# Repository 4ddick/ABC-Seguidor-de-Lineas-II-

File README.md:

Seguidor-de-linea-ABCII
Seguidor de linea modelo ABC (versión.II)

Durante el presente año, los integrantes del equipo "ABC" han asumido el compromiso de desarrollar un nuevo diseño del proyecto previo denominado "Robot seguidor de línea ABC I". El rediseño contempla modificaciones estructurales y funcionales orientadas a optimizar el desempeño del sistema, incrementar la precisión en el seguimiento de trayectorias y mejorar la interacción con el usuario.

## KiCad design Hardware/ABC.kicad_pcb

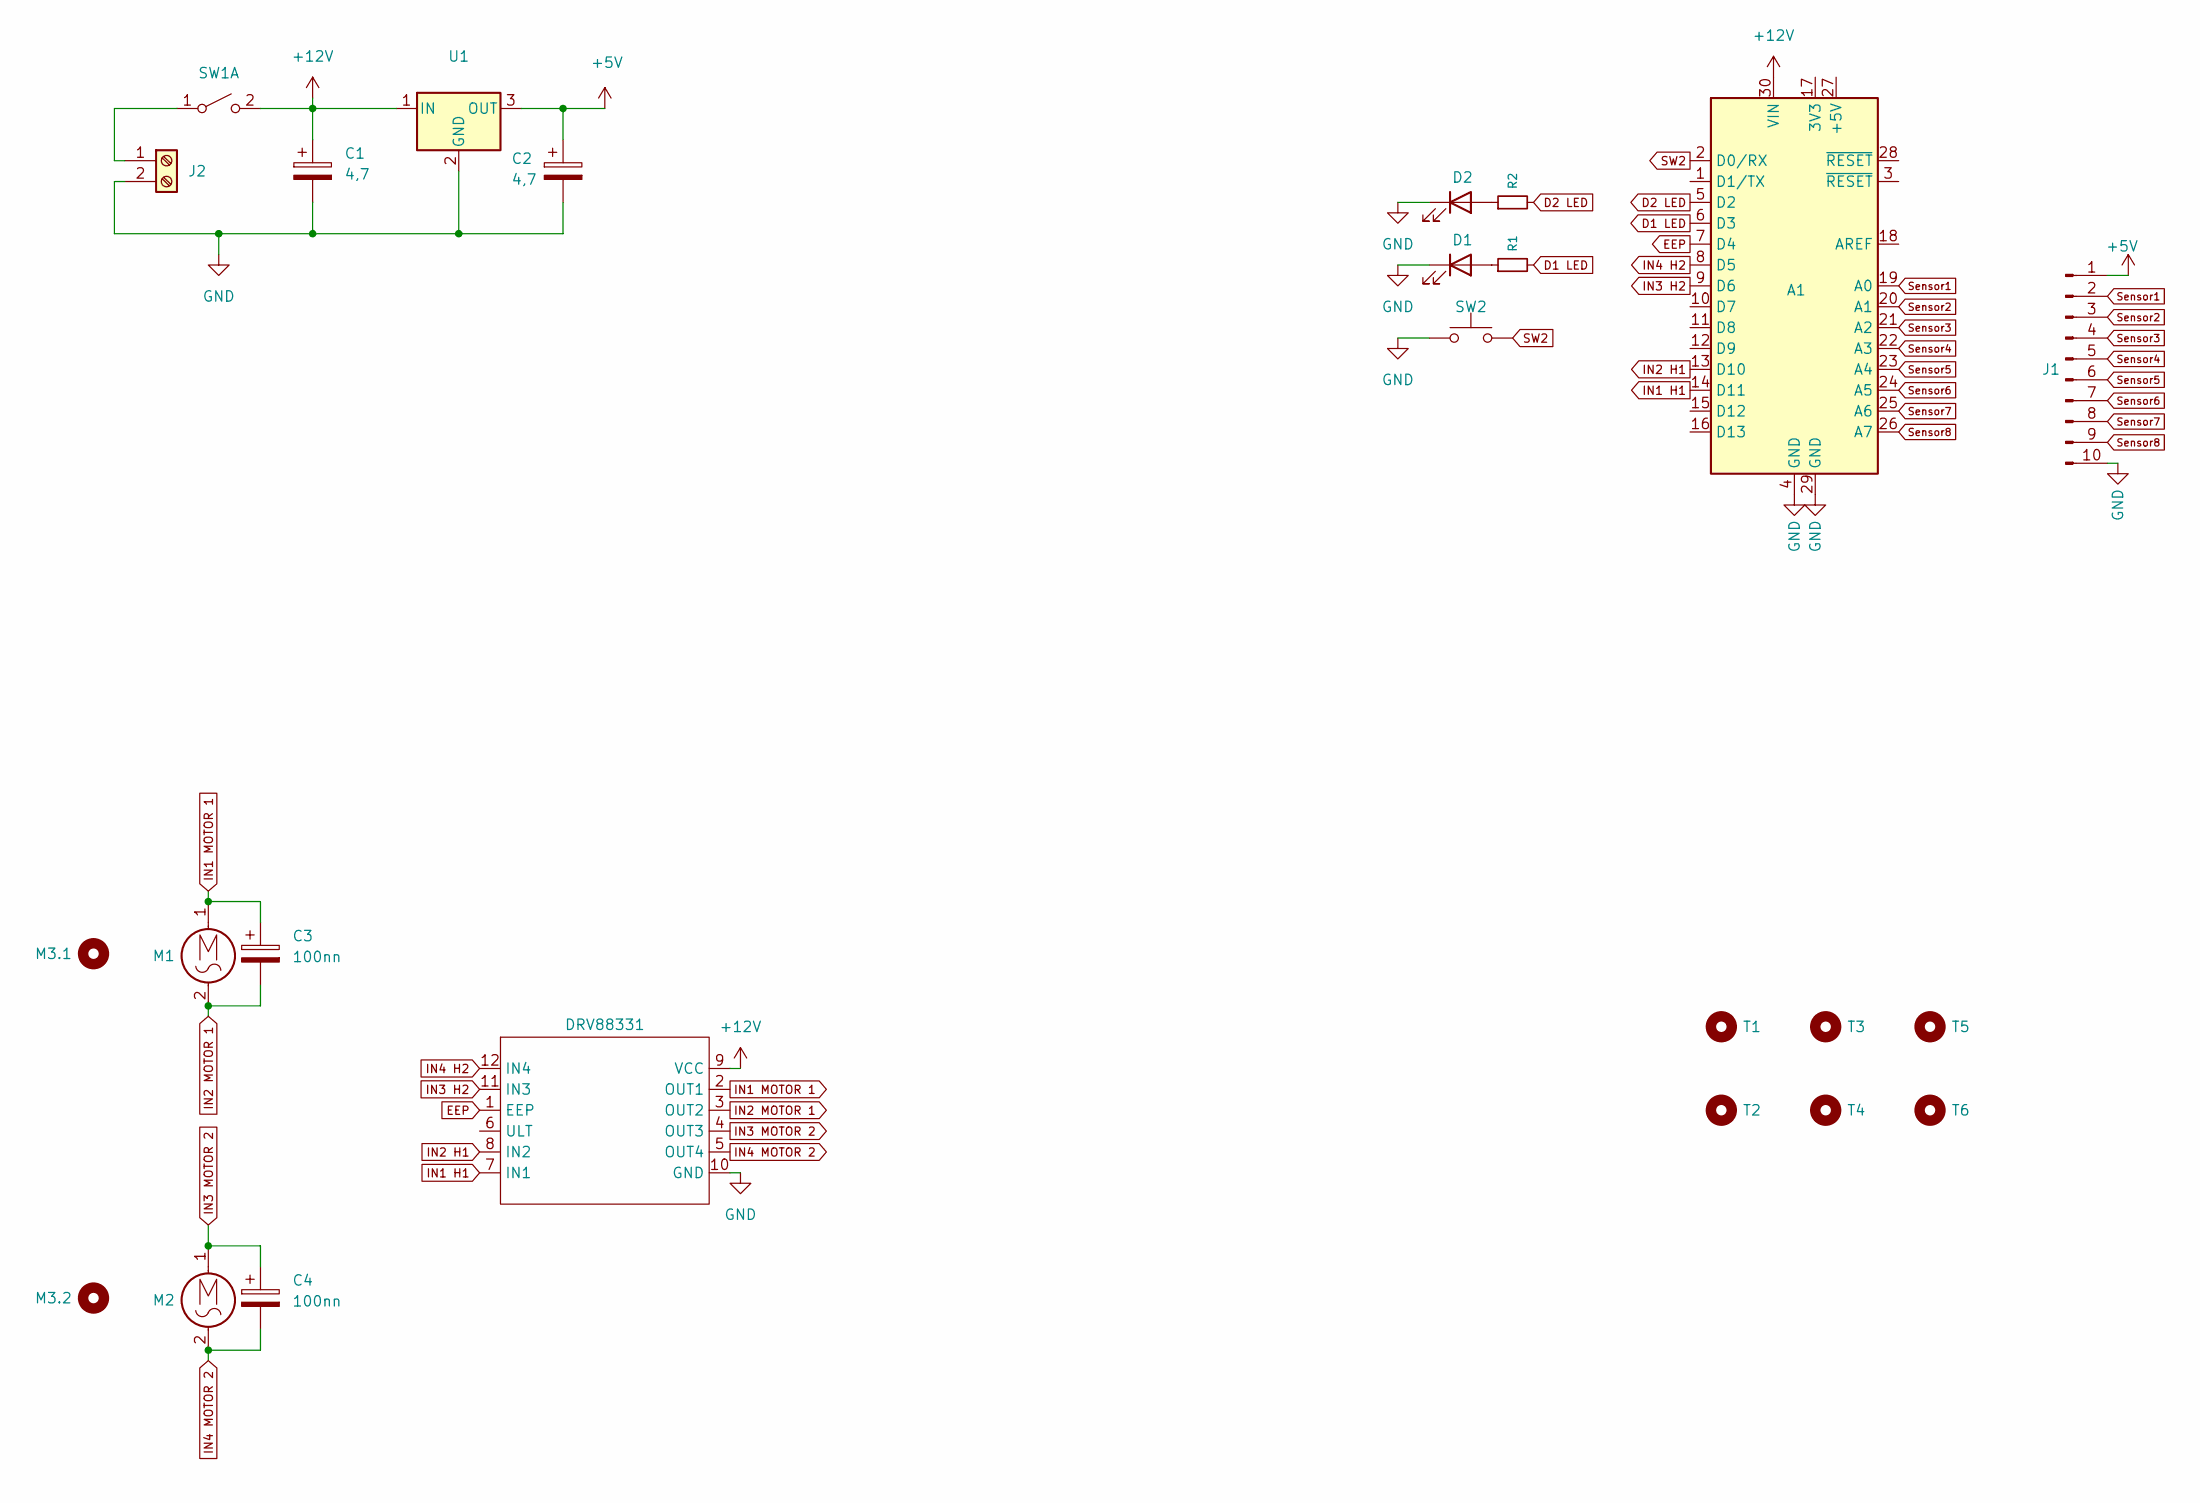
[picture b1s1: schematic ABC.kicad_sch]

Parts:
A1: Arduino_Nano_v2.x; Arduino_Nano
C1, C2: 4,7; CP_Radial_D6.3mm_P2.50mm
C3, C4: 100nn; C_Disc_D5.0mm_W2.5mm_P5.00mm
D1, D2: LED; LED_D5.0mm
DRV88331: PUENTE H1; DRV8833_MODULE
J1: Conn_01x10_Pin; PinHeader_1x10_P2.54mm_Vertical
J2: XT30AWM
M1, M2: Motor_AC; PinHeader_1x02_P2.54mm_Vertical
M3.1, M3.2: Mounting_Hole; Pololu_Micro_Bracket_Wheel_42mm
R1, R2: R_Small; R_Axial_DIN0207_L6.3mm_D2.5mm_P7.62mm_Horizontal
SW1: SW_DPST_x2; TerminalBlock_MaiXu_MX126-5.0-03P_1x03_P5.00mm
SW2: SW_PUSH; Button
T1, T2, T3, T4, T5, T6: Mounting_Hole; MountingHole_3.2mm_M3
U1: L7805; TO-220-3_Vertical

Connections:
+5V: C2.1, J1.1, U1.3 (OUT)
+12V: A1.30 (VIN), C1.1, DRV88331.9 (VCC), SW1.2 (B), SW1.3 (A), U1.1 (IN)
D1 LED: A1.6 (D3), R1.2
D2 LED: A1.5 (D2), R2.2
EEP: A1.7 (D4), DRV88331.1 (EEP)
GND: A1.4 (GND), A1.29 (GND), C1.2, C2.2, D1.1 (K), D2.1 (K), DRV88331.10 (GND), J1.10, J2.2, SW2.1, U1.2 (GND)
IN1 H1: A1.14 (D11), DRV88331.7 (IN1)
IN1 MOTOR 1: C3.1, DRV88331.2 (OUT1), M1.1
IN2 H1: A1.13 (D10), DRV88331.8 (IN2)
IN2 MOTOR 1: C3.2, DRV88331.3 (OUT2), M1.2
IN3 H2: A1.9 (D6), DRV88331.11 (IN3)
IN3 MOTOR 2: C4.1, DRV88331.4 (OUT3), M2.1
IN4 H2: A1.8 (D5), DRV88331.12 (IN4)
IN4 MOTOR 2: C4.2, DRV88331.5 (OUT4), M2.2
unnamed: D1.2 (A), R1.1
unnamed: D2.2 (A), R2.1
unnamed: J2.1, SW1.1 (A)
SW2: A1.2 (D0/RX), SW2.2
Sensor1: A1.19 (A0), J1.2
Sensor2: A1.20 (A1), J1.3
Sensor3: A1.21 (A2), J1.4
Sensor4: A1.22 (A3), J1.5
Sensor5: A1.23 (A4), J1.6
Sensor6: A1.24 (A5), J1.7
Sensor7: A1.25 (A6), J1.8
Sensor8: A1.26 (A7), J1.9

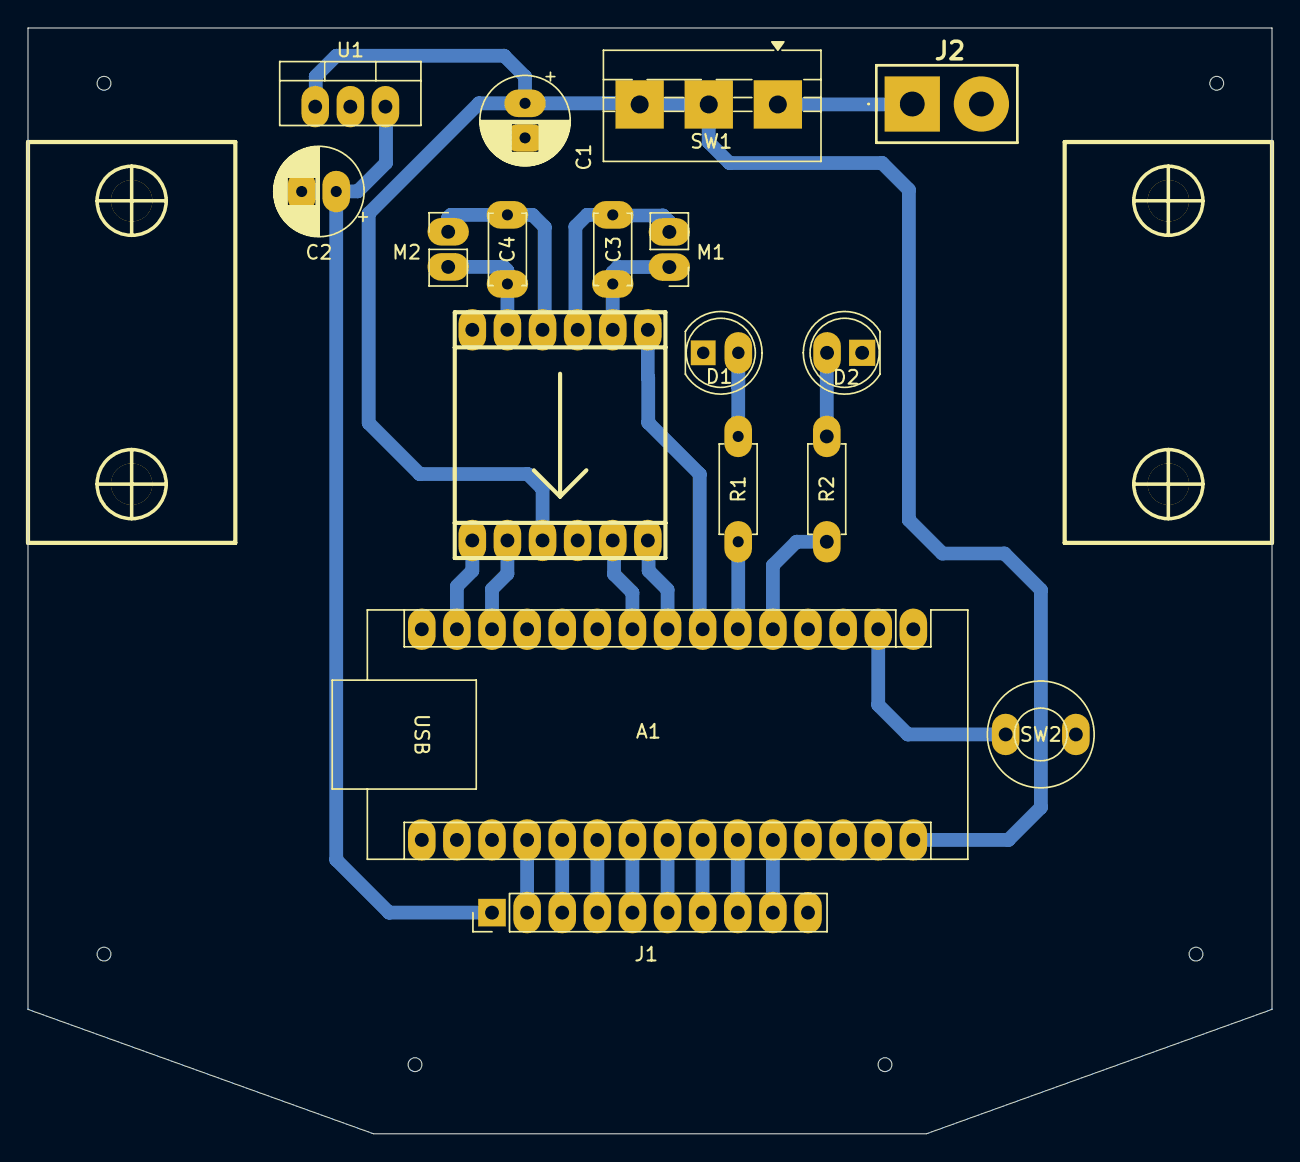
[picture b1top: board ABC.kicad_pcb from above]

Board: 2 copper layers, 90.0 x 80.0 mm, 25 parts (0 on the bottom side), 26 nets.

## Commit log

2026-04-30 placa
2026-04-30 Seguidor-de-linea-ABCII
    Seguidor de linea modelo ABC (versión.II)
    Durante el presente año, los integrantes del equipo "ABC" han asumido el compromiso de desarrollar un nuevo diseño del proyecto previo denominado "Robot seguidor de línea ABC I". El rediseño contempl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
2026-06-19 19/6
2026-06-19 19/63D
